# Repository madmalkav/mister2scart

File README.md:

# Disclaimer

This device has been designed by someone that doesn't have a clue about electronics. If you decide to build it and use it, you do it on your own responisibility.

# MISTER2SCART

This PCB is designed to connect a MiSTer VGA and audio analog output to a SCART RGB device using standard VGA and SCART cables. It includes a switch to set the TV to 4:3 or 16:9, and a RCA connector for lightguns that may require it.

The device is designed for **RGB output only**, it will probably not work with composite or s-video signals.

The device expects **5V from VGA** pin 9, if you use it with a HDMI to VGA dongle in Direct Video, it may not work, as some of these dongles doesn't provide this voltage.

# Components

You are going to need:

- A female SCART connector like Ninigi SCART-17 , Kycon K-SCARTX-022 or similar. These are getting harder to find on the usual component shops but they are plenty available on Aliexpress.
- A female 3.5mm stereo jack with a footprint similar to SJ1-3523NG or similar. These are available both in component shops and Aliexpress.
- A female RCA connector, with footprint like  BOOMELE AV-5, Kobiconn 156-0098-E, Kycon KLPX-0848-2-BL and similars.
- A 470 Ohms, 1/4W resistor. The PCB is designed for a resistor of 6.3mm length.
- A sliding SPDT switch, I used SS12D10G6-WJ but again, anything with the same footprint should do.
- A MAX662ACPA IC, used to generate 12V for the 4:3 / 16:9 selection. 
- 2x MLCC 220nF 50V ±20% capacitors, with a 5.08mm distance between legs.
- 2x Tantalum 4.7uF 16V ±10%, with a distance of 2.54mm between legs.
- A VGA female connector, with a clearance from the pins to the edge of the PCB of ~3.08mm

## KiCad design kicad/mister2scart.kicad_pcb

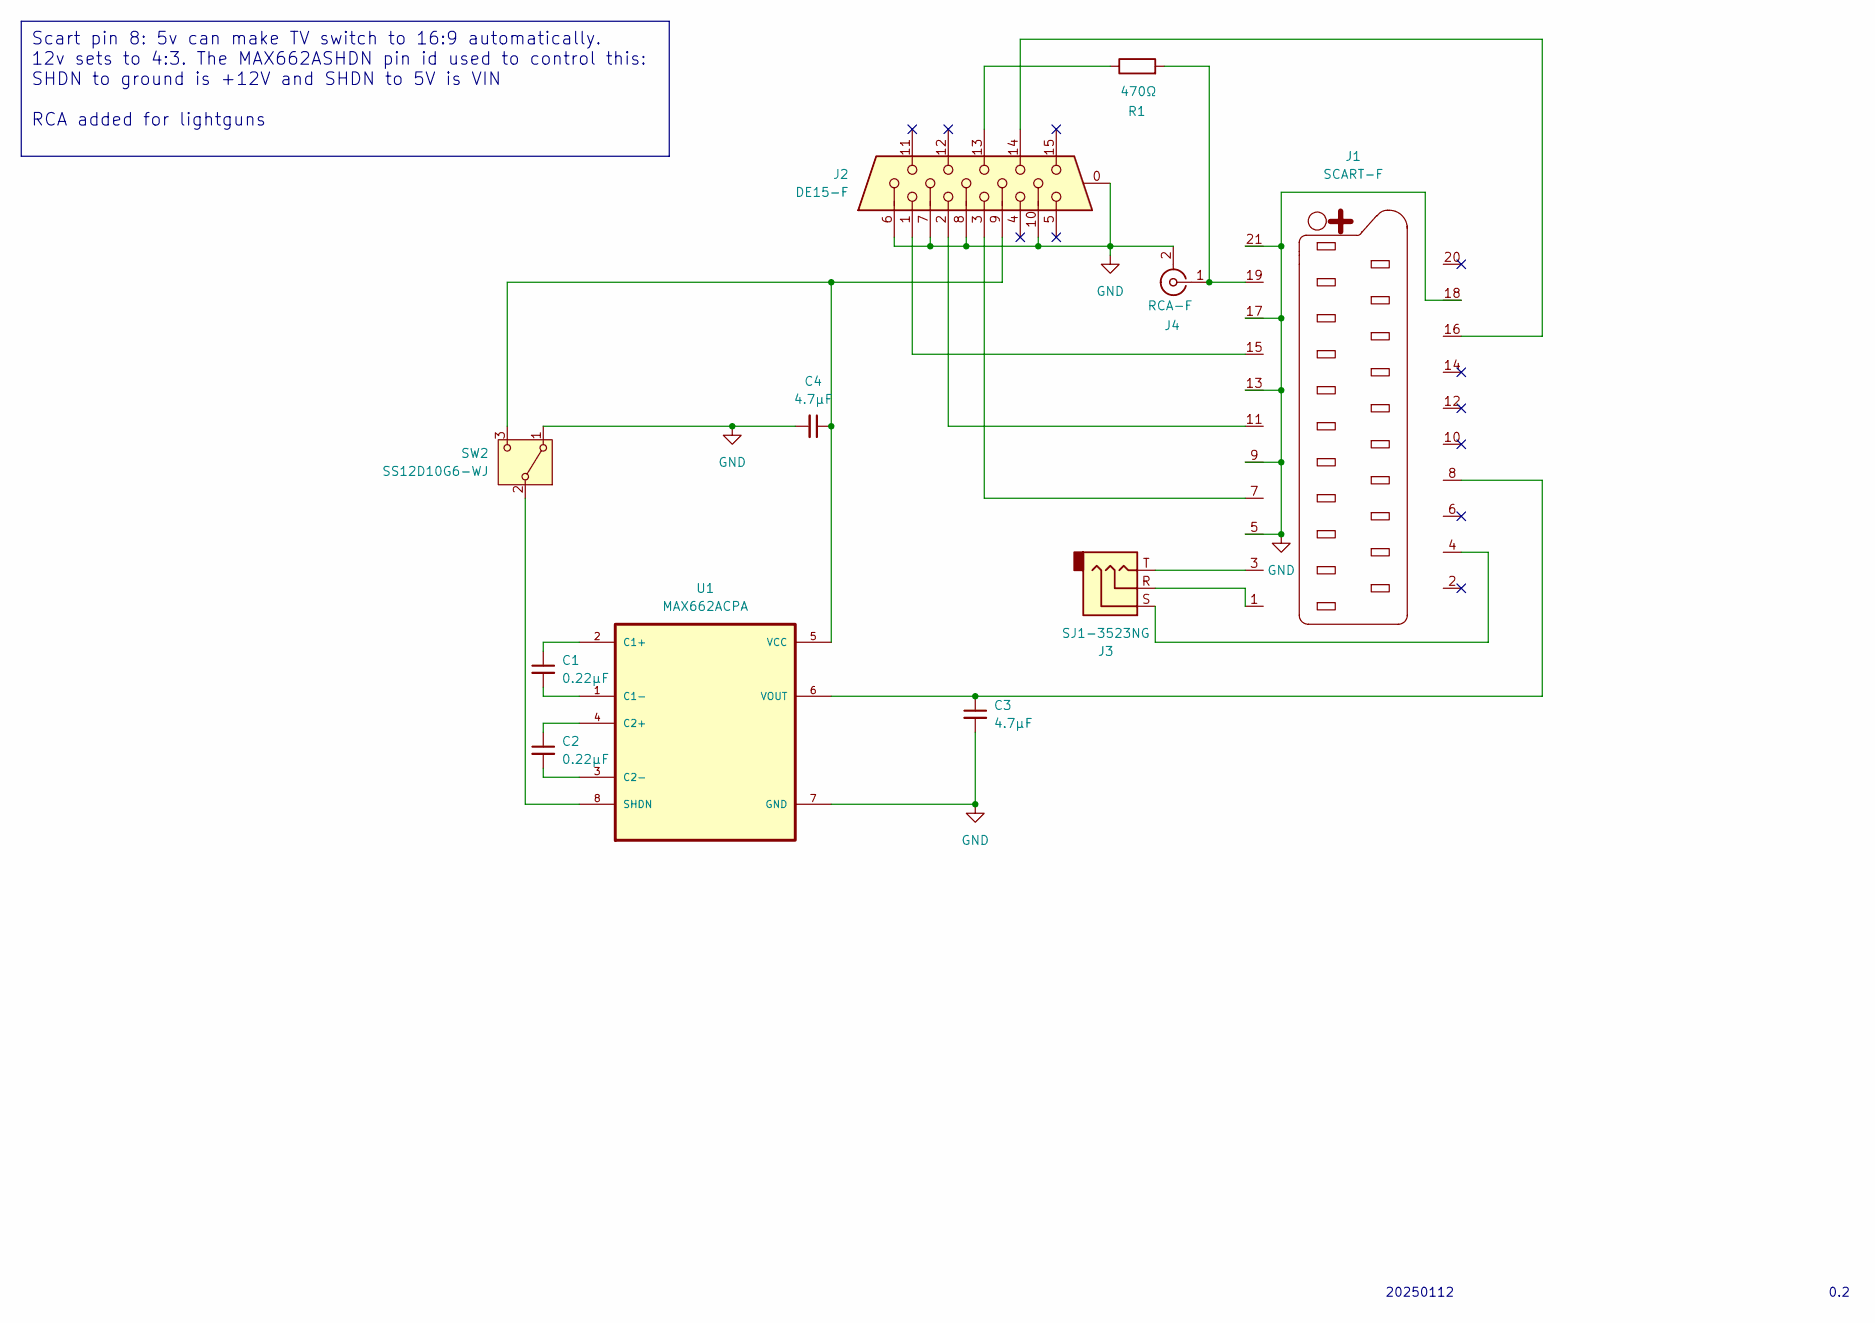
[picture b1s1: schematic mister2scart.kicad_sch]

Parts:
C1, C2: 0.22μF; CAP-TH_L5.1-W3.2-P5.08-D0.50; LCSC PN C1621936
C3, C4: 4.7μF; C_Disc_D5.0mm_W2.5mm_P2.50mm; LCSC PN C18164672
J1: SCART-F; KYCON_SCART_K-SCARTX-022_Horizontal
J2: DE15-F; DSUB-15-HD_Female_Horizontal_P2.29x1.90mm_EdgePinOffset3.03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; LCSC PN C3038673
J3: SJ1-3523NG; Jack_3.5mm_CUI_SJ1-3523N_Horizontal; LCSC PN C4992449
J4: RCA-F; CONN-TH_AV-5; LCSC PN C18080
R1: 470Ω; R_Axial_DIN0207_L6.3mm_D2.5mm_P10.16mm_Horizontal
SW2: SS12D10G6-WJ; SW-TH_3P-P4.80_HX-SS12D10G6-WJ; LCSC PN C19189125
U1: MAX662ACPA; DIP794W47P254L991H457Q8; LCSC PN C1355736

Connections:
GND: C3.2, C4.2, J1.5, J1.9, J1.13, J1.17, J1.18, J1.21, J2.0, J2.6, J2.7, J2.8, J2.10, J4.2 (Ext), SW2.1 (A), U1.7 (GND)
unnamed: J1.1, J3.R
unnamed: J1.3, J3.T
unnamed: J1.4, J3.S
unnamed: J1.7, J2.3
unnamed: C3.1, J1.8, U1.6 (VOUT)
unnamed: J1.11, J2.2
unnamed: J1.15, J2.1
unnamed: J1.16, J2.14
unnamed: J1.19, J4.1 (In), R1.2
unnamed: J2.13, R1.1
unnamed: SW2.2 (B), U1.8 (SHDN)
unnamed: C4.1, J2.9, SW2.3 (C), U1.5 (VCC)
unnamed: C1.1, U1.2 (C1+)
unnamed: C1.2, U1.1 (C1-)
unnamed: C2.1, U1.4 (C2+)
unnamed: C2.2, U1.3 (C2-)

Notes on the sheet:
20250112
0.2
Scart pin 8: 5v can make TV switch to 16:9 automatically. 12v sets to 4:3. The MAX662ASHDN pin id used to control this: SHDN to ground is +12V and SHDN to 5V is VIN RCA added for lightguns

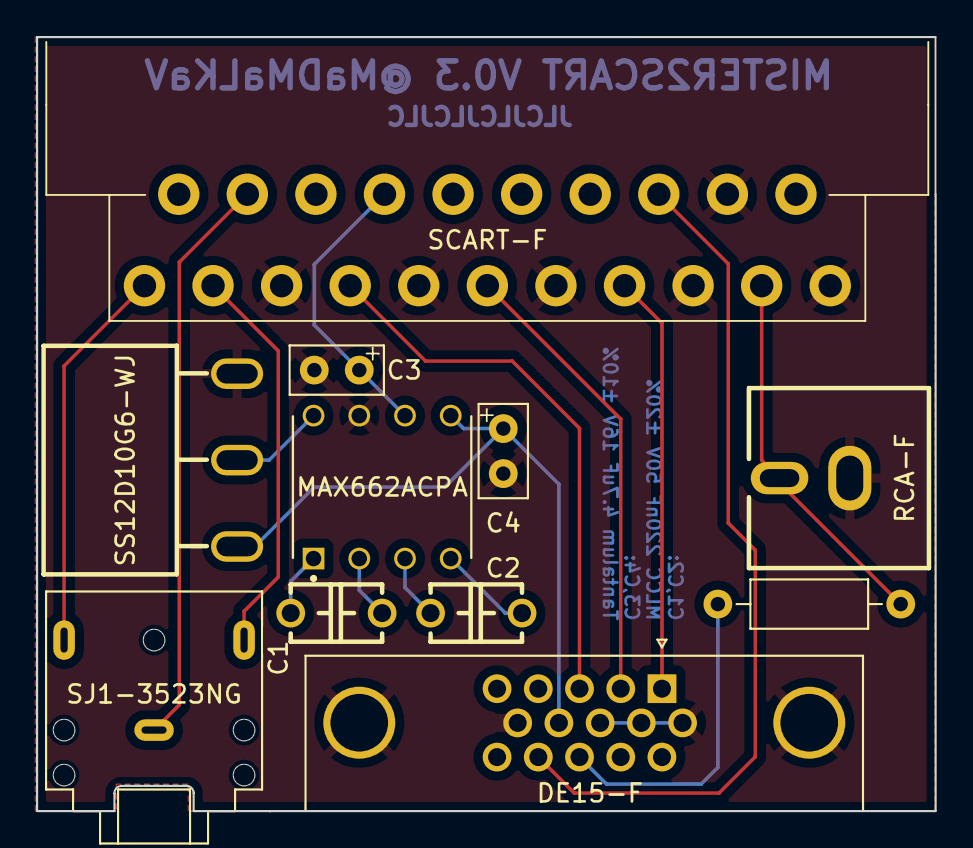
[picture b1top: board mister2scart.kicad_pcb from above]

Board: 2 copper layers, 49.9 x 43.0 mm, 11 parts (0 on the bottom side), 17 nets.

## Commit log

2025-01-13 V0.2:
    - Corrected pinout of the SCART connection, as SCART to SCART cables have some pins crossed.
    - Marked polarity in the silkscreen for polarized capacitors
    - Increase footprint for resistor
2025-04-27 v0.3: fixed sync connector pinout
2025-04-27 Cleanup
2025-05-30 Include schematic PDF
